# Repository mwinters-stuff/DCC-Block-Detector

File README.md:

# DCC Block Detector
Simple DCC Block Detector

Using the schematic from https://sites.google.com/site/gregthrottles/pulse-trans
which is based from someone called "Rob Paisley" and extended by myself to add
a second transistor and pull-up resistors. Fed of ~5 Volts you get approx 4.5v 
on the signal line.

# Schematic

# Render

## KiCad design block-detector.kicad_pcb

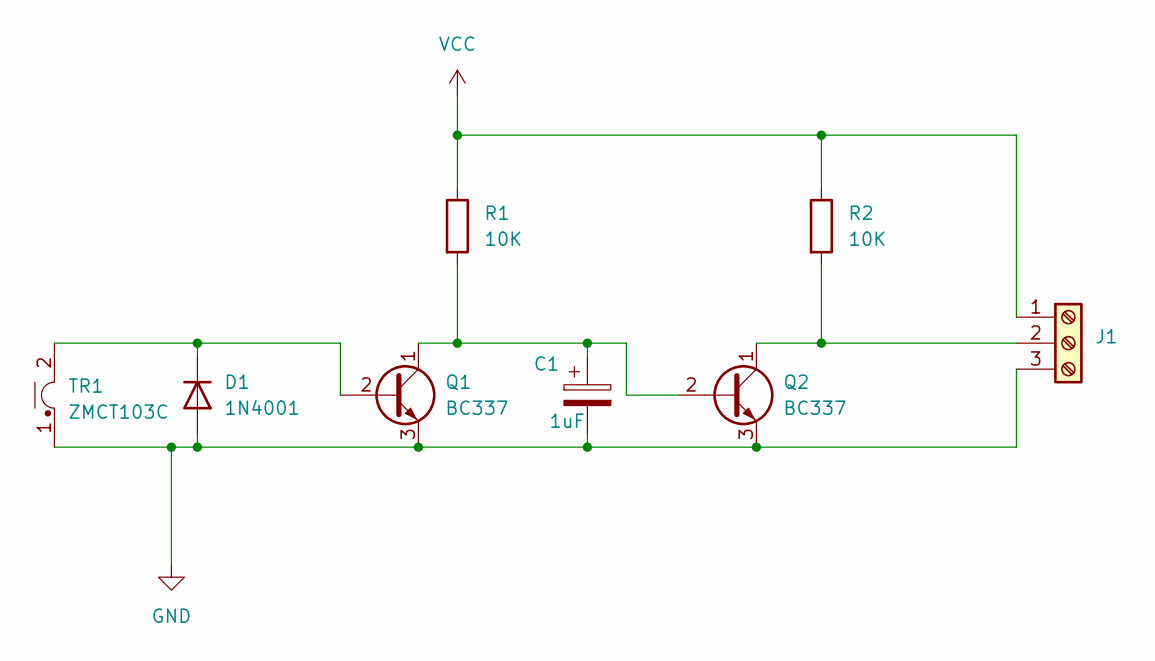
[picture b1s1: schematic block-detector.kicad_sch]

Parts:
C1: 1uF; CP_Radial_D5.0mm_P2.50mm
D1: 1N4001; D_DO-41_SOD81_P10.16mm_Horizontal
J1: KF301-3P
Q1, Q2: BC337; TO-92_Inline
R1, R2: 10K; R_Axial_DIN0207_L6.3mm_D2.5mm_P2.54mm_Vertical
TR1: ZMCT103C; Transformer_Zeming_ZMCT103C

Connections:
GND: C1.2, D1.2 (A), J1.3, Q1.3 (E), Q2.3 (E), TR1.1
unnamed: D1.1 (K), Q1.2 (B), TR1.2
unnamed: J1.2, Q2.1 (C), R2.2
unnamed: C1.1, Q1.1 (C), Q2.2 (B), R1.2
VCC: J1.1, R1.1, R2.1

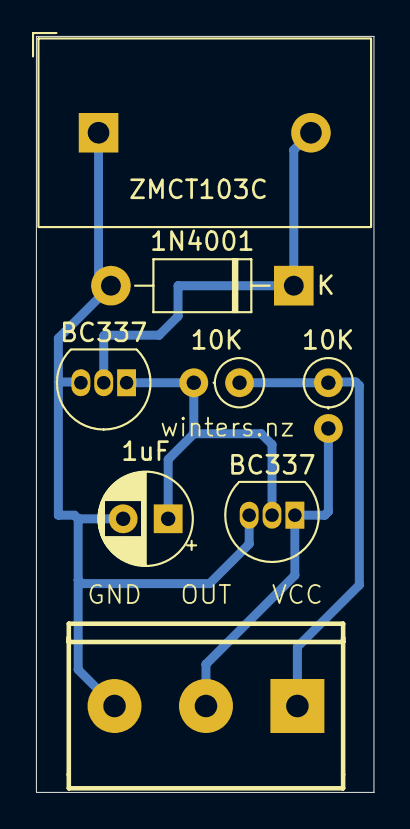
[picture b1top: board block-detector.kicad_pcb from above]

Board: 2 copper layers, 18.8 x 42.0 mm, 8 parts (0 on the bottom side), 5 nets.

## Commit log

2024-11-25 Initial Commit.
2024-12-09 Working schematic and pcb
